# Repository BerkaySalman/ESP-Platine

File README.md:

# ESP-Platine
ESP-Platine mit GCode

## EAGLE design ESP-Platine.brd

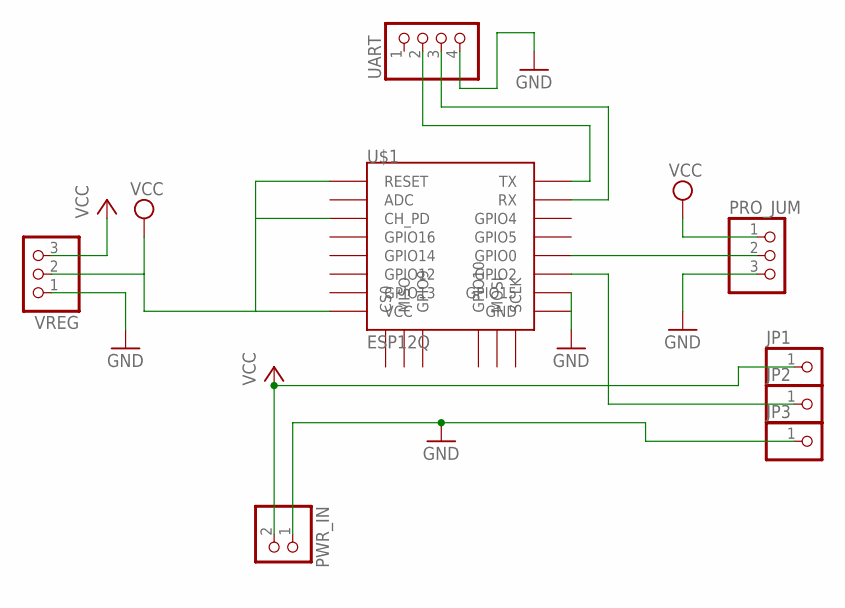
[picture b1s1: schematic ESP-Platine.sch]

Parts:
JP1, JP2, JP3: PINHD-1X1; 1X01
PRO_JUM: PINHD-1X3; 1X03
PWR_IN: PINHD-1X2; 1X02
U$1: ESP12Q
UART: PINHD-1X4; 1X04
VREG: PINHD-1X3; 1X03

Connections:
3V3: PRO_JUM.1, U$1.CH_PD, U$1.RESET, U$1.VCC, VREG.2
5V_IN: JP1.1, PWR_IN.2, VREG.3
GND: JP3.1, PRO_JUM.3, PWR_IN.1, U$1.GND, U$1.GPIO15, UART.4, VREG.1
GPIO0: PRO_JUM.2, U$1.GPIO0
GPIO2: JP2.1, U$1.GPIO2
RX: U$1.RX, UART.3
TX: U$1.TX, UART.2

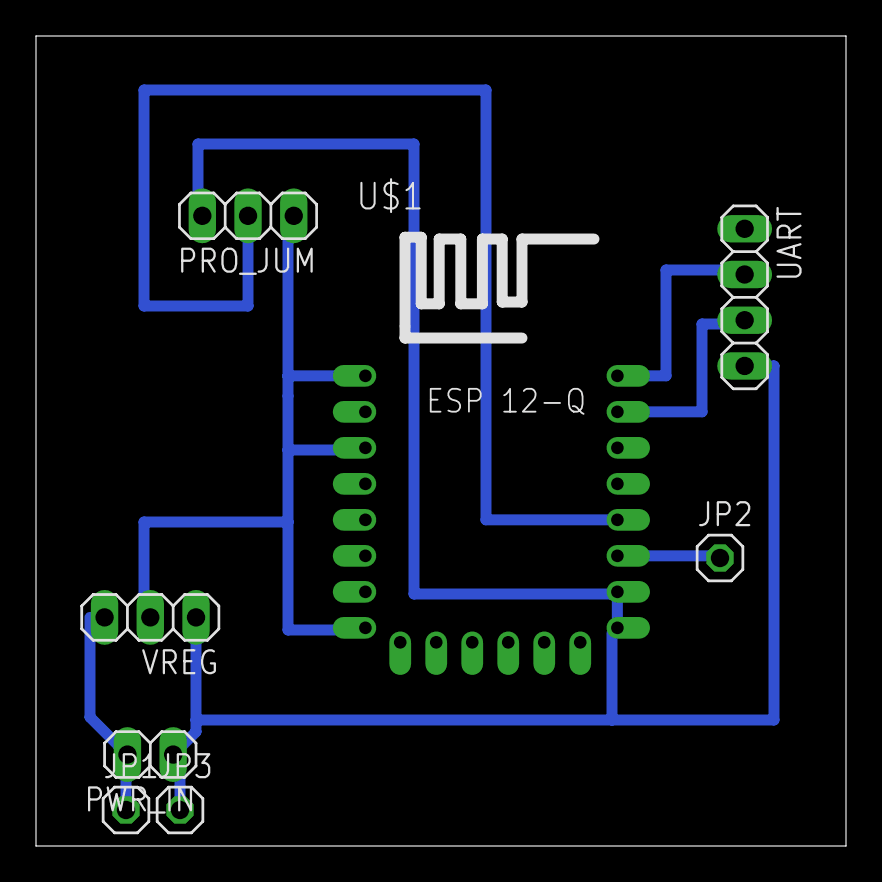
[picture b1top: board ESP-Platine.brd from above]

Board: 2 copper layers, 45.0 x 45.0 mm, 8 parts (0 on the bottom side), 7 nets.
